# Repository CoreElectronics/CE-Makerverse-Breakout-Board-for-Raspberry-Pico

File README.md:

This is the repo for the Core Electronics [Makerverse Breakout Board for Raspberry Pi Pico](https://core-electronics.com.au/catalog/product/view/sku/CE08491).

## License
This project is open source - please review the LICENSE.md file for further licensing information.

If you have any technical questions, or concerns about licensing, please contact technical support on the [Core Electronics forums](https://forum.core-electronics.com.au/).

*\"Makerverse\", "Makerverse Labs" and the Makerverse logo are trademarks of Core Electronics Pty Ltd.*

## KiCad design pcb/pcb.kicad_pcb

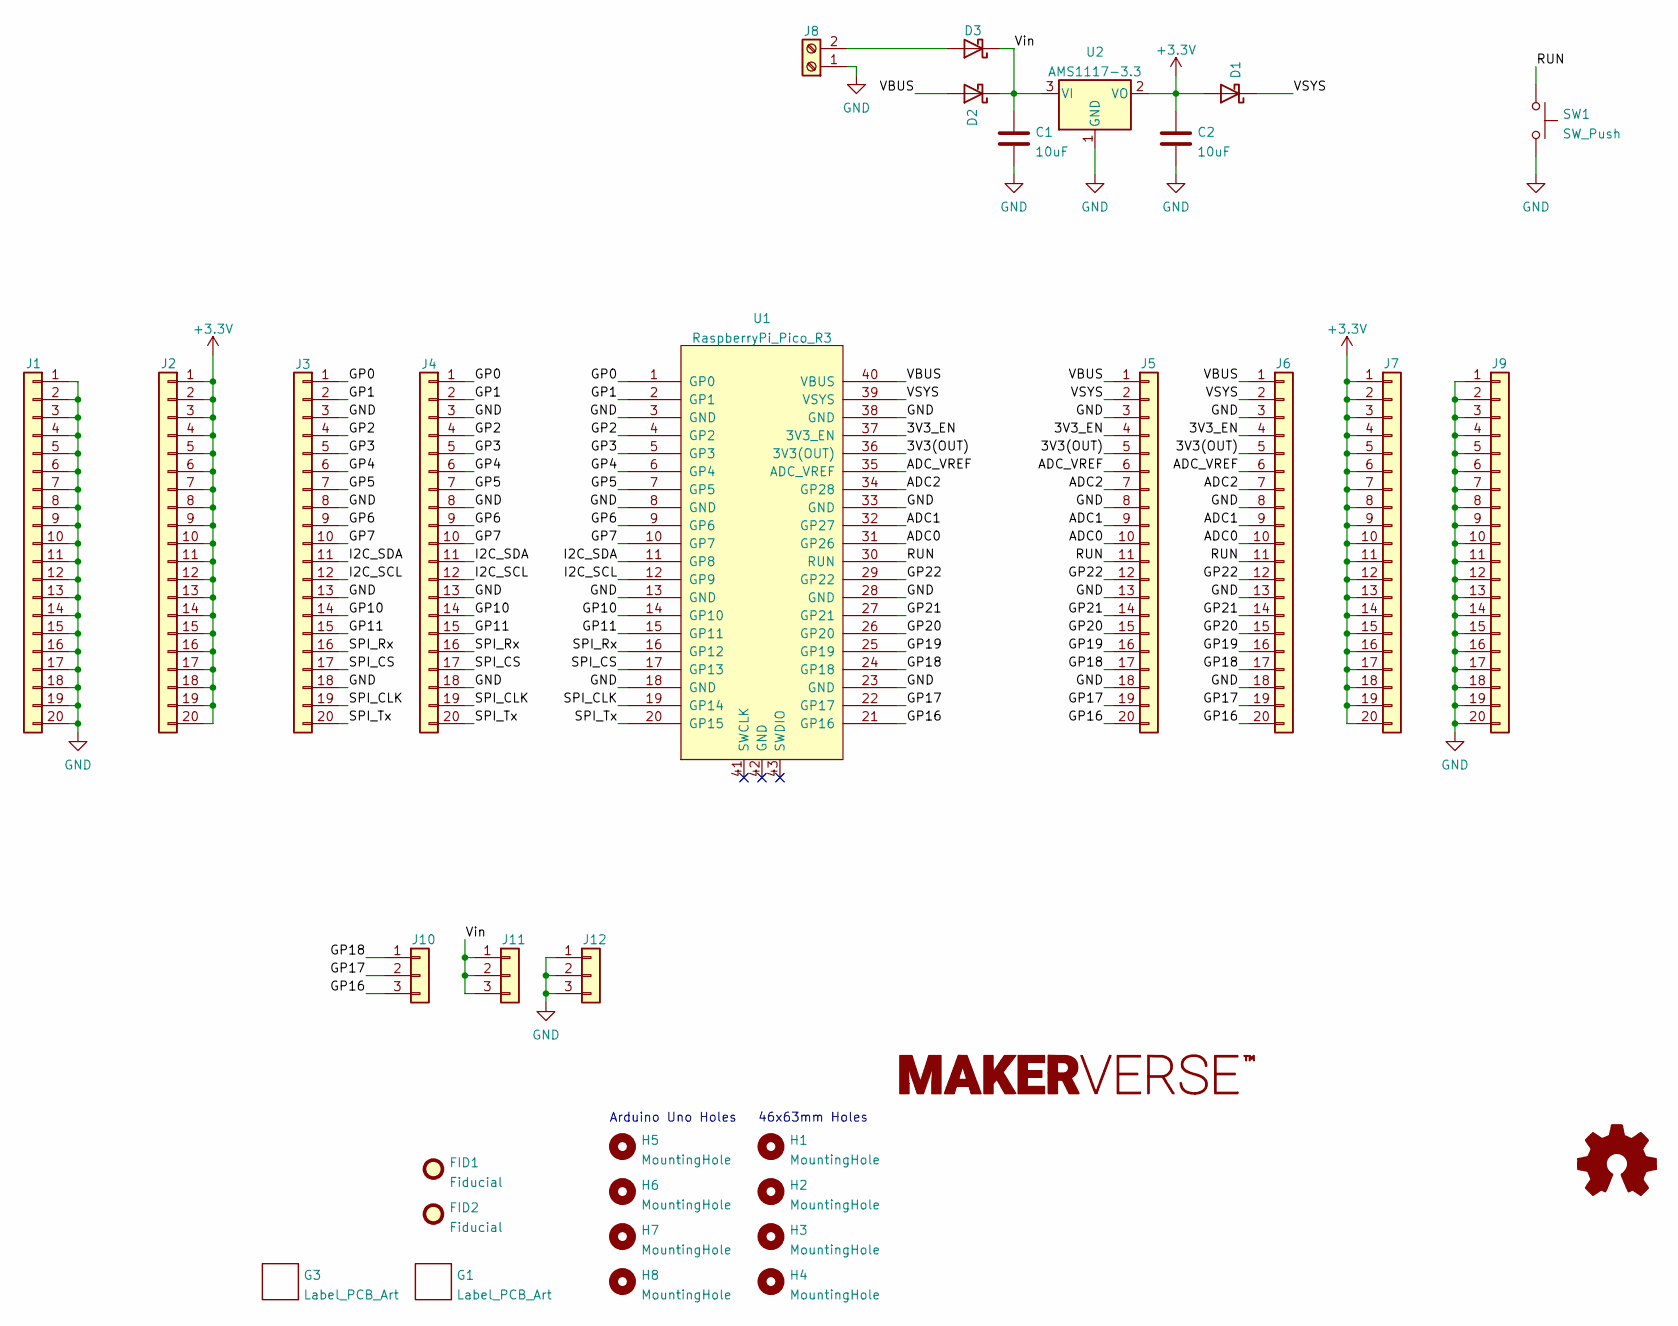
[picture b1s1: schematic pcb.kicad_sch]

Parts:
C1, C2: 10uF; C_0603_1608Metric
D1, D2, D3: D_Schottky; D_SMA
FID1, FID2: Fiducial; Fiducial_1mm_Mask2mm
G1: Label_PCB_Art; CE08491
G2: LOGO_Makerverse; makerverse_logo_35.8x4.2mm
G3: Label_PCB_Art; usb_ico
H1, H2, H3, H4, H5, H6, H7, H8: MountingHole; MountingHole_3.2mm_M3
J1, J2, J3, J4, J5, J6, J7, J9: Conn_01x20; PinSocket_1x20_P2.54mm_Vertical-Large-Pads
J8: Screw_Terminal_01x02; Screw-Terminal-2_P5.00mm
J10, J11, J12: Conn_01x03; PinHeader_1x03_P2.54mm_Vertical-Large-Pads
LOGO1: Logo_Open_Hardware_Small; oshw_3.9x3.5mm
SW1: SW_Push; SW_Tactile_5x5
U1: RaspberryPi_Pico_R3
U2: AMS1117-3.3; SOT-89-3

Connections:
+3V3: C2.1, D1.2 (A), J2.1, J2.2, J2.3, J2.4, J2.5, J2.6, J2.7, J2.8, J2.9, J2.10, J2.11, J2.12, J2.13, J2.14, J2.15, J2.16, J2.17, J2.18, J2.19, J2.20, J7.1, J7.2, J7.3, J7.4, J7.5, J7.6, J7.7, J7.8, J7.9, J7.10, J7.11, J7.12, J7.13, J7.14, J7.15, J7.16, J7.17, J7.18, J7.19, J7.20, U2.2 (VO)
/3V3(OUT): J5.5, J6.5, U1.36 (3V3(OUT))
/3V3_EN: J5.4, J6.4, U1.37 (3V3_EN)
/ADC0: J5.10, J6.10, U1.31 (GP26)
/ADC1: J5.9, J6.9, U1.32 (GP27)
/ADC2: J5.7, J6.7, U1.34 (GP28)
/ADC_VREF: J5.6, J6.6, U1.35 (ADC_VREF)
/GP0: J3.1, J4.1, U1.1 (GP0)
/GP1: J3.2, J4.2, U1.2 (GP1)
/GP2: J3.4, J4.4, U1.4 (GP2)
/GP3: J3.5, J4.5, U1.5 (GP3)
/GP4: J3.6, J4.6, U1.6 (GP4)
/GP5: J3.7, J4.7, U1.7 (GP5)
/GP6: J3.9, J4.9, U1.9 (GP6)
/GP7: J3.10, J4.10, U1.10 (GP7)
/GP10: J3.14, J4.14, U1.14 (GP10)
/GP11: J3.15, J4.15, U1.15 (GP11)
/GP16: J5.20, J6.20, J10.3, U1.21 (GP16)
/GP17: J5.19, J6.19, J10.2, U1.22 (GP17)
/GP18: J5.17, J6.17, J10.1, U1.24 (GP18)
/GP19: J5.16, J6.16, U1.25 (GP19)
/GP20: J5.15, J6.15, U1.26 (GP20)
/GP21: J5.14, J6.14, U1.27 (GP21)
/GP22: J5.12, J6.12, U1.29 (GP22)
/I2C_SCL: J3.12, J4.12, U1.12 (GP9)
/I2C_SDA: J3.11, J4.11, U1.11 (GP8)
/RUN: J5.11, J6.11, SW1.1, U1.30 (RUN)
/SPI_CLK: J3.19, J4.19, U1.19 (GP14)
/SPI_CS: J3.17, J4.17, U1.17 (GP13)
/SPI_Rx: J3.16, J4.16, U1.16 (GP12)
/SPI_Tx: J3.20, J4.20, U1.20 (GP15)
/VBUS: D2.2 (A), J5.1, J6.1, U1.40 (VBUS)
/VSYS: D1.1 (K), J5.2, J6.2, U1.39 (VSYS)
/Vin: C1.1, D2.1 (K), D3.1 (K), J11.1, J11.2, J11.3, U2.3 (VI)
GND: C1.2, C2.2, J1.1, J1.2, J1.3, J1.4, J1.5, J1.6, J1.7, J1.8, J1.9, J1.10, J1.11, J1.12, J1.13, J1.14, J1.15, J1.16, J1.17, J1.18, J1.19, J1.20, J3.3, J3.8, J3.13, J3.18, J4.3, J4.8, J4.13, J4.18, J5.3, J5.8, J5.13, J5.18, J6.3, J6.8, J6.13, J6.18, J8.1, J9.1, J9.2, J9.3, J9.4, J9.5, J9.6, J9.7, J9.8, J9.9, J9.10, J9.11, J9.12, J9.13, J9.14, J9.15, J9.16, J9.17, J9.18, J9.19, J9.20, J12.1, J12.2, J12.3, SW1.2, U1.3 (GND), U1.8 (GND), U1.13 (GND), U1.18 (GND), U1.23 (GND), U1.28 (GND), U1.33 (GND), U1.38 (GND), U2.1 (GND)
unnamed: D3.2 (A), J8.2

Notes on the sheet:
Arduino Uno Holes
46x63mm Holes

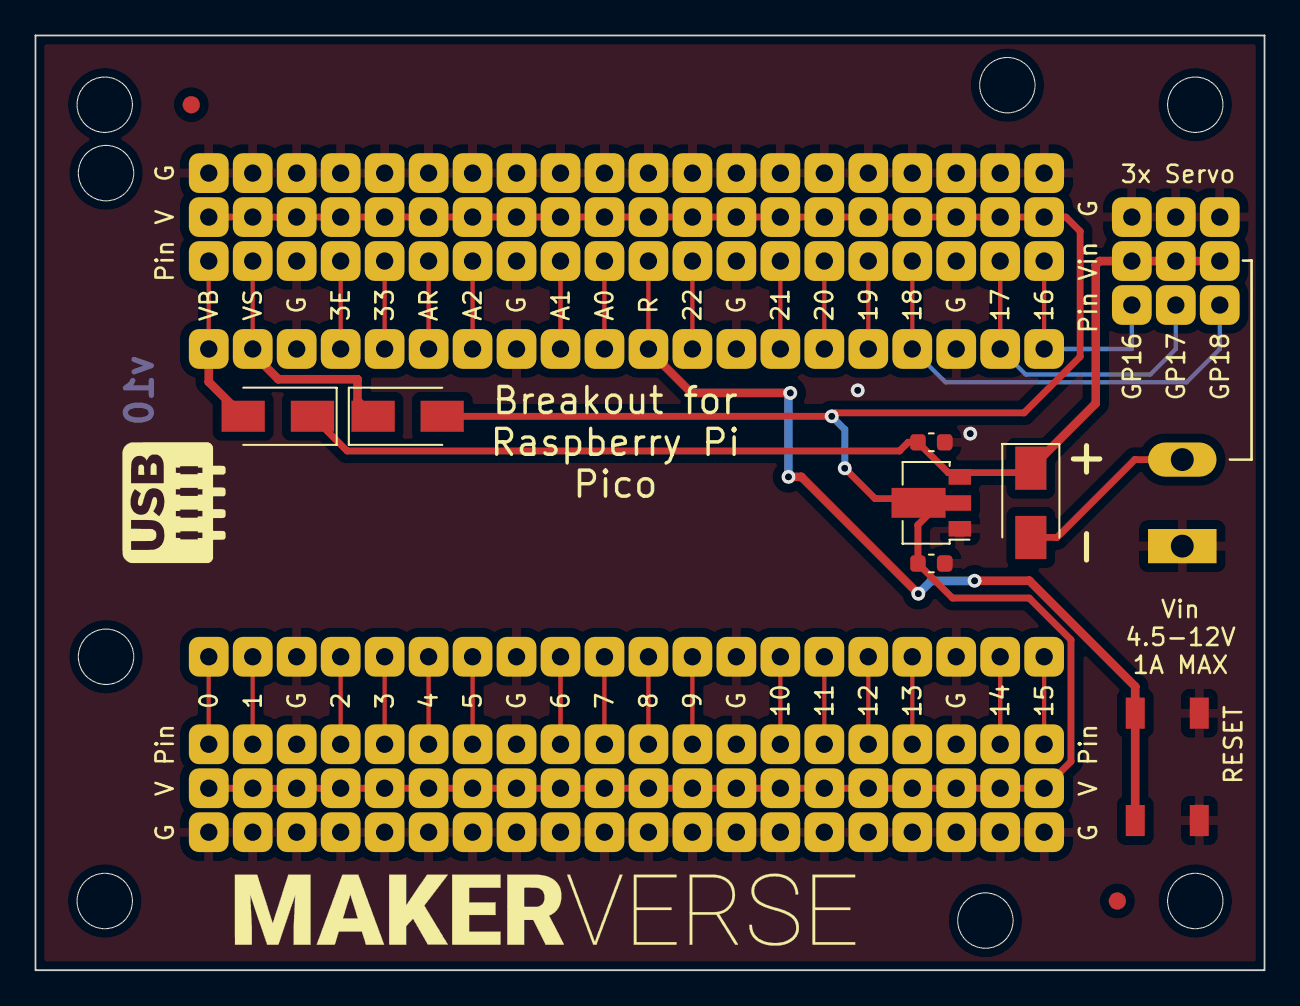
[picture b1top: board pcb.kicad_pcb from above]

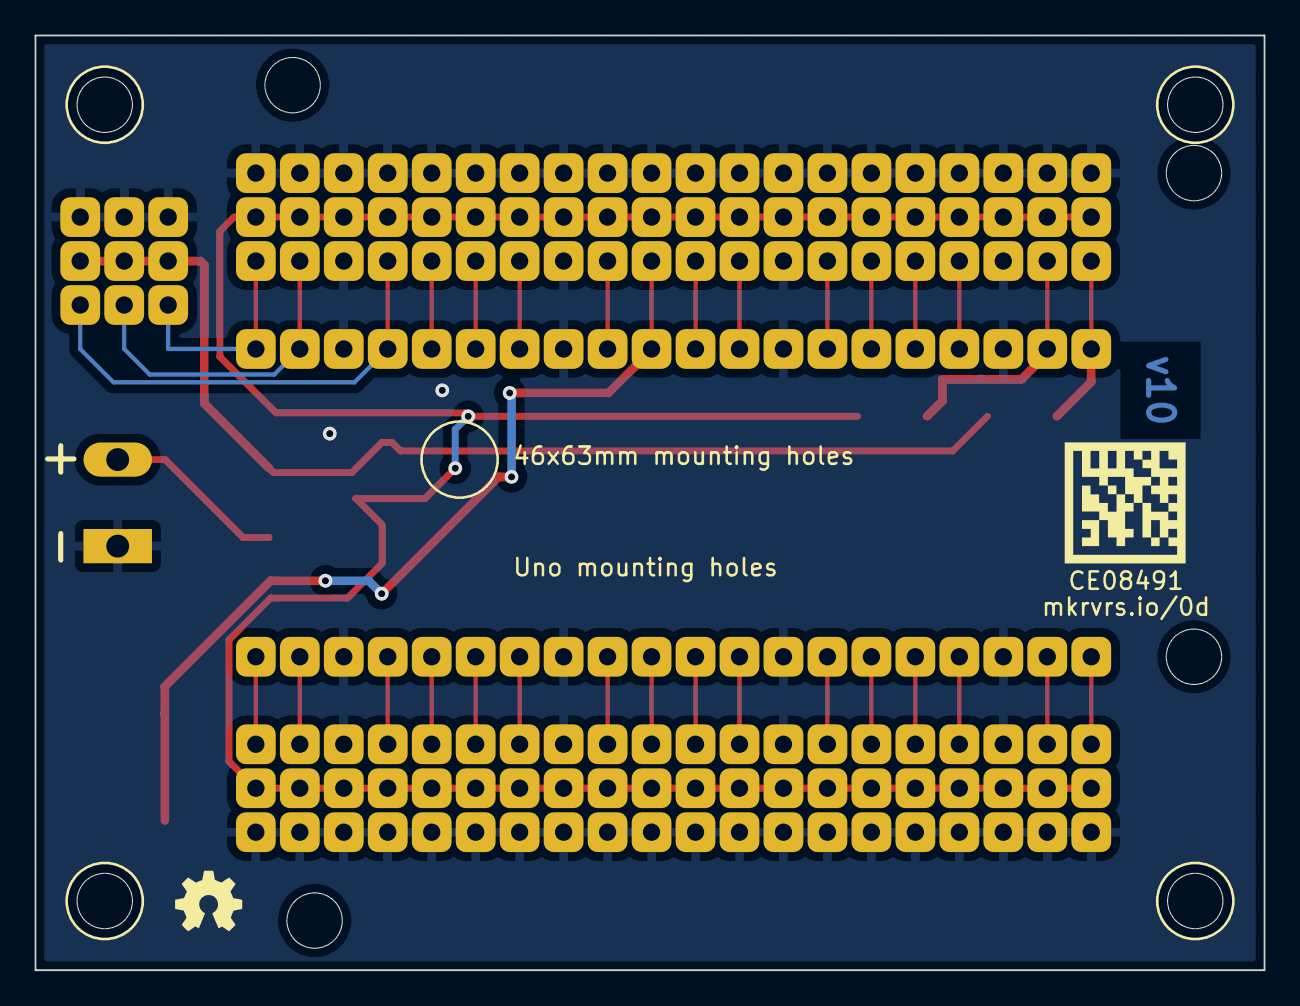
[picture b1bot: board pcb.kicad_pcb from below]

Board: 2 copper layers, 71.0 x 54.0 mm, 33 parts (2 on the bottom side), 36 nets.

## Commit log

2022-10-05 add schematic PDF
